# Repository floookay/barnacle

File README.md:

# barnacle

The barnacle is unibody ortho keyboard with an Alice-like split on the pinky columns and a fixed layout that's compatible with keycap set base kits.

## inspiration + backstory

The Boardrun series was my main inspiration for this project obviously. I desperately wanted to get an acrylic frosted purple Boardrun classic but things happend so that's not likely anymore unfortunatelly.

The creativity of designers with colorful keycap designs and interesting keyboards (like the TGR Alice) got me hooked with the hobby. I exclusively switched to non-rowstagger keyboards a couple of years ago and realized that I own a lot of beautiful keycaps that I love but can't use because of these weird non-symmetrical larger-than-1.5u mod key sizes per row. Most ergonomic keyboard designs that are trying to solve that issue, I don't find aesthetically pleasing or don't like the layout.  
So I've set out to create my own: the barnacle

## design goals

- 5x6 unibody ortho keyboard
- base kit compatibility
- 3d printable on 220mm build plates
- symmetric design (AMAP)
- outer thumb keys next to space bars
- easily expandable later on
- minimize stabilizer use

## layout

The main layout is fixed but the cores offer some variety. This is based on my Sol keymap but you can modify it in QMK of course.
<details>
<summary>layout</summary>

</details>

## pcb

This keyboard uses the [0xCB Helios](https://keeb.supply/products/0xcb-helios) as its controller. It's an affordable open-source pro-micro-compatible RP2040 controller with ESD protection and additional pins and features.

The pcbs where designed with KiCAD 8.0

### core pcb

You can use any core pcb with a shell. They are smaller than 100mmx100mm so it's relativly cheap to get a small batch made.

#### basic core

This core offers the following configurations:
- 9 keys
- 3 keys and a encoder with a big knob
- 3 keys and a 0.96" OLED screen
- 2 small encoders, 1 key and a 0.96" OLED screen
- a central encoder with the biggest knob

### shell pcb

- fixed layout, so I chose hotswap sockets
- rgb underglow
- per key rgb

## case

- 3mm acrylic bottom
- 5 degree typing angle
- designed for 3d printing
- sandwich mount
- exchangable core pieces

The case was designed with FreeCAD 0.21.2

## firmware

This keyboard is powered by QMK: <https://github.com/floookay/qmk_firmware/keyboards/barnacle>

## bom and assembly

For the bill of materials and assembly instructions see [here](./assembly.md).

## ideas and/or stuff I'd like to add in the future

### pcb

- [ ] *bluetooth core* with a nice!nano and without RGB (maybe with a safety cover toggle switch or sth)
- [ ] *trackball core* with PMW3360 sensor
- [ ] *trackpad core* with a 40mm GlidePoint Cirque Trackpad
- [ ] *oled core* with a large (colored?) OLED screen
- [ ] *lumberjack core* with a window and an integrated controller
- [ ] *rgb core* with a window and a rgb matrix
- [ ] *audio core* with a speaker/beeper

### case

- [ ] *brick core* with brick plate on top
- [ ] *wood core* with a cutout wooden window piece
- [ ] *gridfinity core* with a spot for a gridfinity bin
- [ ] *phone core* with a holder for (small) phones, maybe with a magsafe charger
- [ ] *change core* with a tray for coins and stuff
- [ ] *pen core* with a hole that fits a pen

### firmware

- [ ] *ZMK support* with the bluetooth core
- [ ] *vial and/or via support* once merged to main branch

## misc

> Why is it called barnacle?

I thought of hermit crabs when I was thinking of similiarities in nature. I stuck with the crab theme, but changed the name to barnacle, because it's a fun word to say out loud.

## acknowledgements

Huge thank you to ebastler and MarvFPV for the awesome [marbastlib](https://github.com/ebastler/marbastlib) library for KiCAD.

Thanks for reading and feel free to reach out to me or create PRs if you have any questions or things to improve upon.

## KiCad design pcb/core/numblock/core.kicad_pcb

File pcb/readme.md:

# pcb

## shell pcb

The shell has a fixed layout with hotswap sockets as well as RGB underglow und per key RBG leds.

## core pcb

You can use any core pcb with a shell. They are smaller than 100mmx100mm so it's relativly cheap to get a small batch made.

> [!NOTE]
> Every core has two jumpers at the top next to the controller. If you want to use RGB leds you will have to bridge either the left or right pads each.
> - Left jumper pad for the input pin: left (marked) for the Helios' pin 25, right for other controllers (D1)
> - Right jumper pad for the power source: left (marked) for raw/5V, right for 3.3V

### versatile core

This is a great starting point if you want to experiment with different layouts and don't care too much about hot swap ability.

The following configurations are supported:
- 9 keys
- 3 keys and a encoder with a big knob
- 3 keys and a 0.96"/1.3" OLED screen
- 2 small encoders, 1 key and a 0.96" OLED screen
- a central encoder with the biggest knob

> [!NOTE]
> There are two additional jumpers on this pcb. These are used so the GND pad of the encoder isn't connected to a column. If you want to use the adjacent key you'll have to close it.

### encoder core

This core has three top keys and a encoder beneath like the versatile core but with hot swap sockets.

### special core

This core exposes I2C and SPI pins and has a large cutout for mounting a trackball, trackpad or large oled to the core case (WIP).

### cute core

This core has centered 2x2 grid of keys with hot swap sockets.

### numpad core

This core has a 3x3 grid of keys with hot swap sockets (when possible) and an additional 0 key that can be snapped off.

### _template/ directory

The `_template/` directory contains the basic configuration if you want to create your own core pcb.

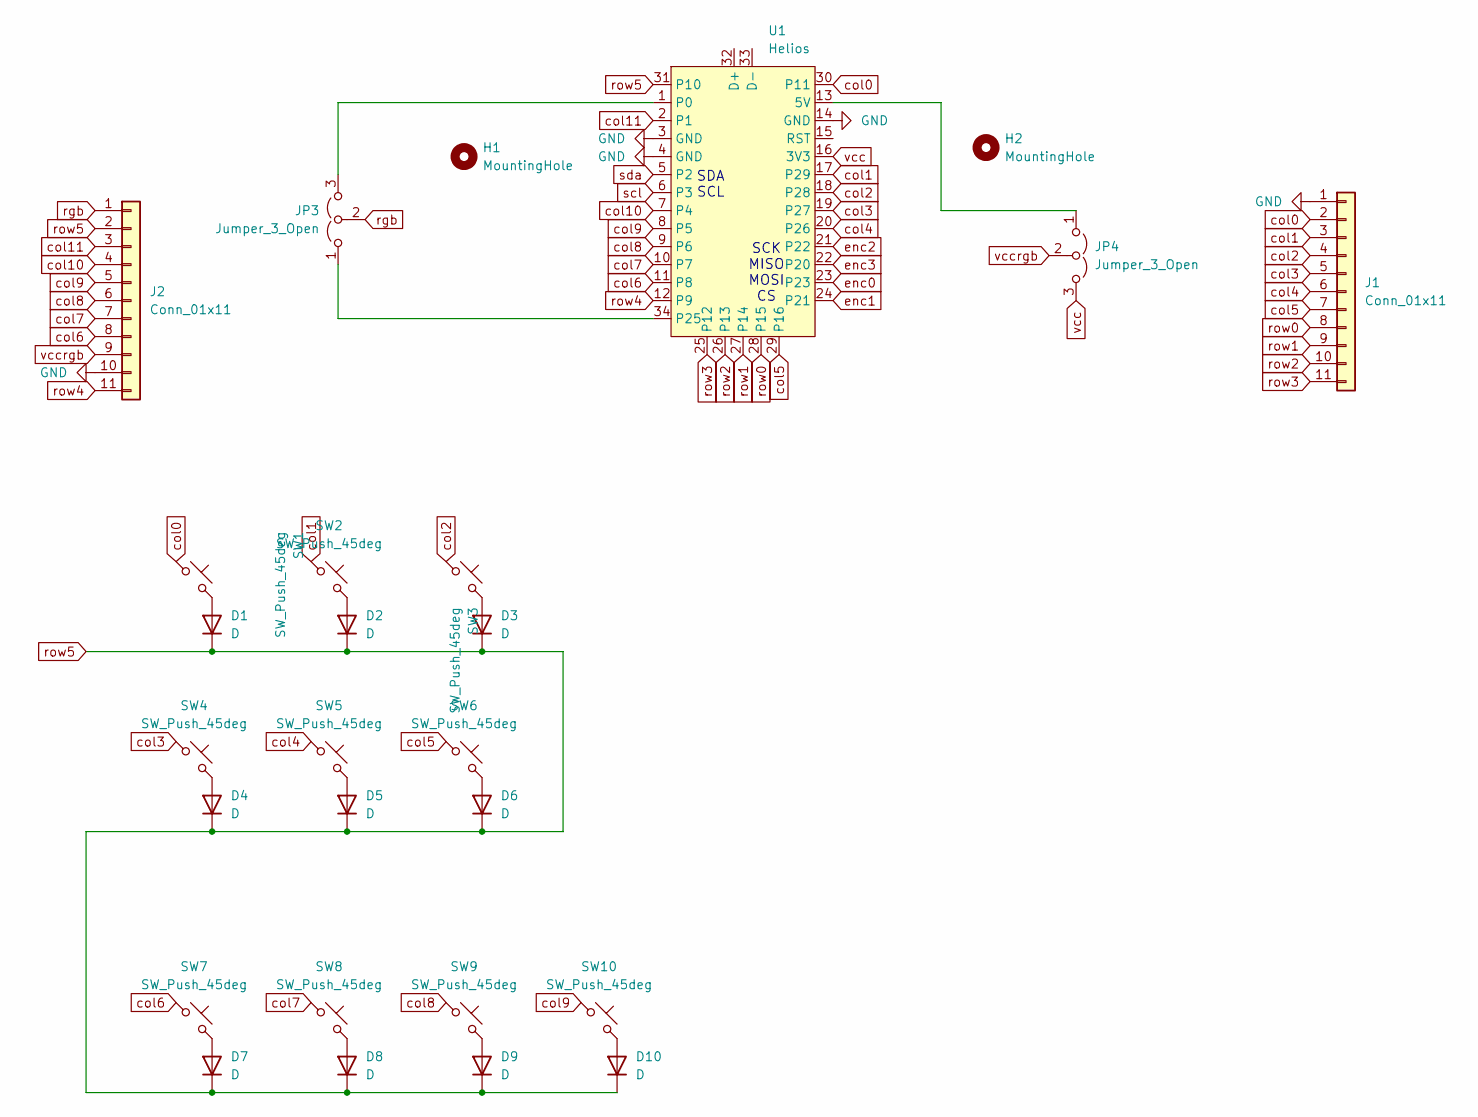
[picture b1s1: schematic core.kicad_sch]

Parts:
D1, D2, D3, D4, D5, D6, D7, D8, D9, D10: D; D_SOD-123-minimal
H1, H2: MountingHole; MountingHole_3.2mm_M3_DIN965_Pad
J1, J2: Conn_01x11; PinHeader_1x11_P2.54mm_Vertical
JP3, JP4: Jumper_3_Open; SolderJumper-3_P1.3mm_Open_RoundedPad1.0x1.5mm
SW1, SW3, SW4, SW5, SW6, SW7, SW8, SW9, SW10: SW_Push_45deg; SW_MX_HS_S_CPG151101S11_1u
SW2: SW_Push_45deg; SW_MX_1u
U1: Helios; Helios_AH_USBup

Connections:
GND: J1.1, J2.10, U1.3 (GND), U1.4 (GND), U1.14 (GND)
unnamed: D1.2 (A), SW1.2
unnamed: D2.2 (A), SW2.2
unnamed: D3.2 (A), SW3.2
unnamed: D4.2 (A), SW4.2
unnamed: D5.2 (A), SW5.2
unnamed: D6.2 (A), SW6.2
unnamed: D7.2 (A), SW7.2
unnamed: D8.2 (A), SW8.2
unnamed: D9.2 (A), SW9.2
unnamed: D10.2 (A), SW10.2
unnamed: JP3.1 (A), U1.34 (P25)
unnamed: JP3.3 (B), U1.1 (P0)
unnamed: JP4.1 (A), U1.13 (5V)
col0: J1.2, SW1.1, U1.30 (P11)
col1: J1.3, SW2.1, U1.17 (P29)
col2: J1.4, SW3.1, U1.18 (P28)
col3: J1.5, SW4.1, U1.19 (P27)
col4: J1.6, SW5.1, U1.20 (P26)
col5: J1.7, SW6.1, U1.29 (P16)
col6: J2.8, SW7.1, U1.11 (P8)
col7: J2.7, SW8.1, U1.10 (P7)
col8: J2.6, SW9.1, U1.9 (P6)
col9: J2.5, SW10.1, U1.8 (P5)
col10: J2.4, U1.7 (P4)
col11: J2.3, U1.2 (P1)
enc0: U1.23
enc1: U1.24 (P21)
enc2: U1.21 (P22)
enc3: U1.22 (P20)
rgb: J2.1, JP3.2 (C)
row0: J1.8, U1.28 (P15)
row1: J1.9, U1.27 (P14)
row2: J1.10, U1.26 (P13)
row3: J1.11, U1.25 (P12)
row4: J2.11, U1.12 (P9)
row5: D1.1 (K), D2.1 (K), D3.1 (K), D4.1 (K), D5.1 (K), D6.1 (K), D7.1 (K), D8.1 (K), D9.1 (K), D10.1 (K), J2.2, U1.31 (P10)
scl: U1.6 (P3)
sda: U1.5 (P2)
vcc: JP4.3 (B), U1.16 (3V3)
vccrgb: J2.9, JP4.2 (C)

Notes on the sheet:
SDA SCL
SCK MISO MOSI CS

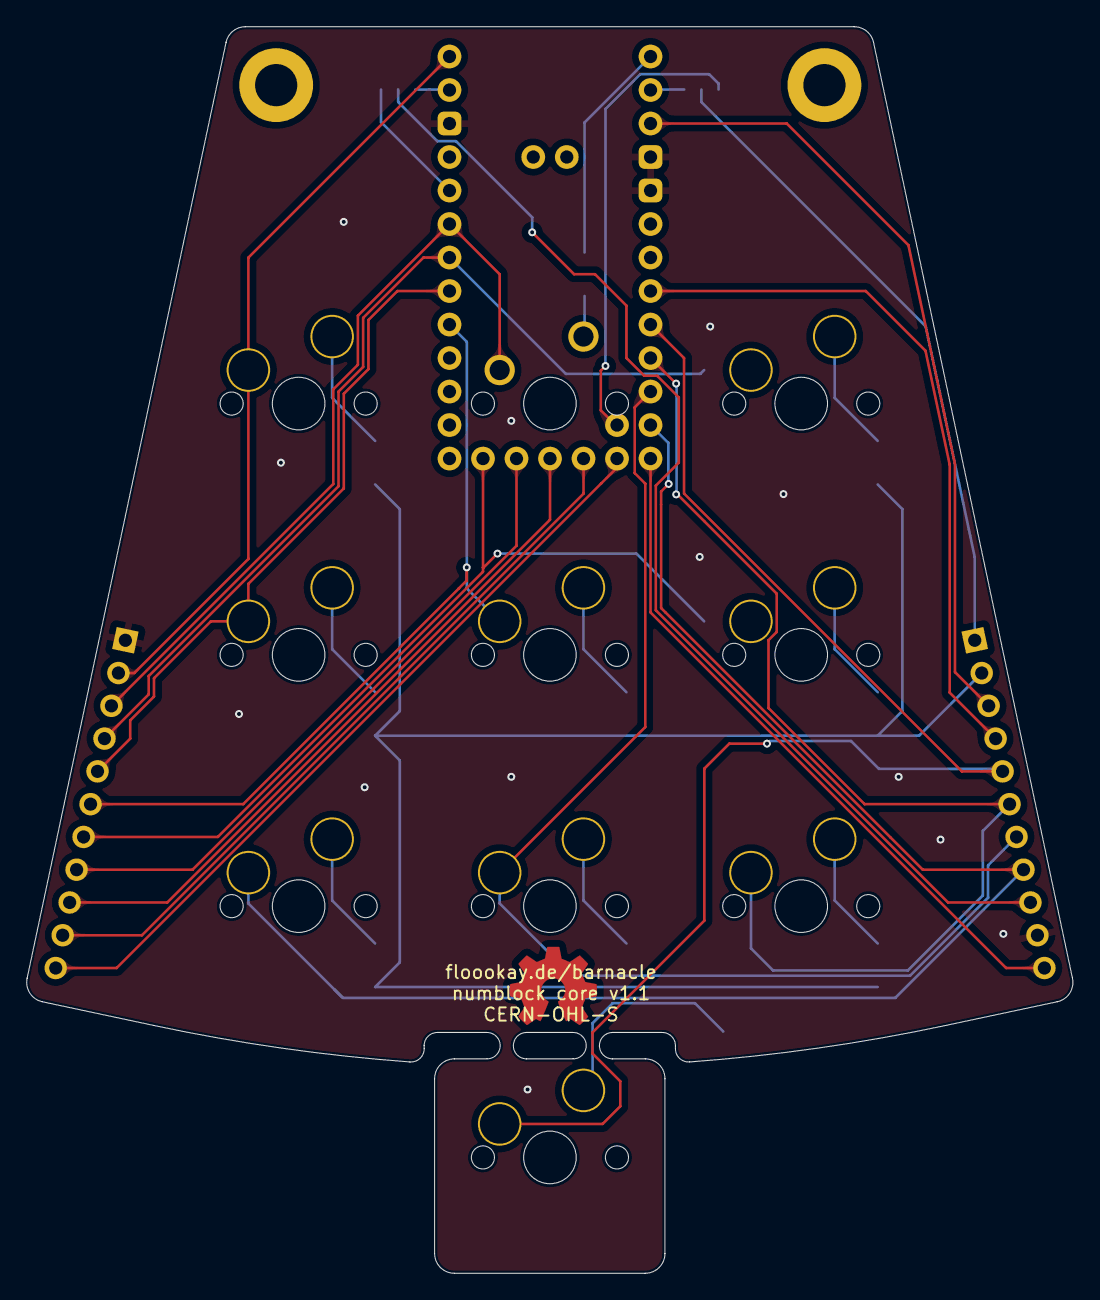
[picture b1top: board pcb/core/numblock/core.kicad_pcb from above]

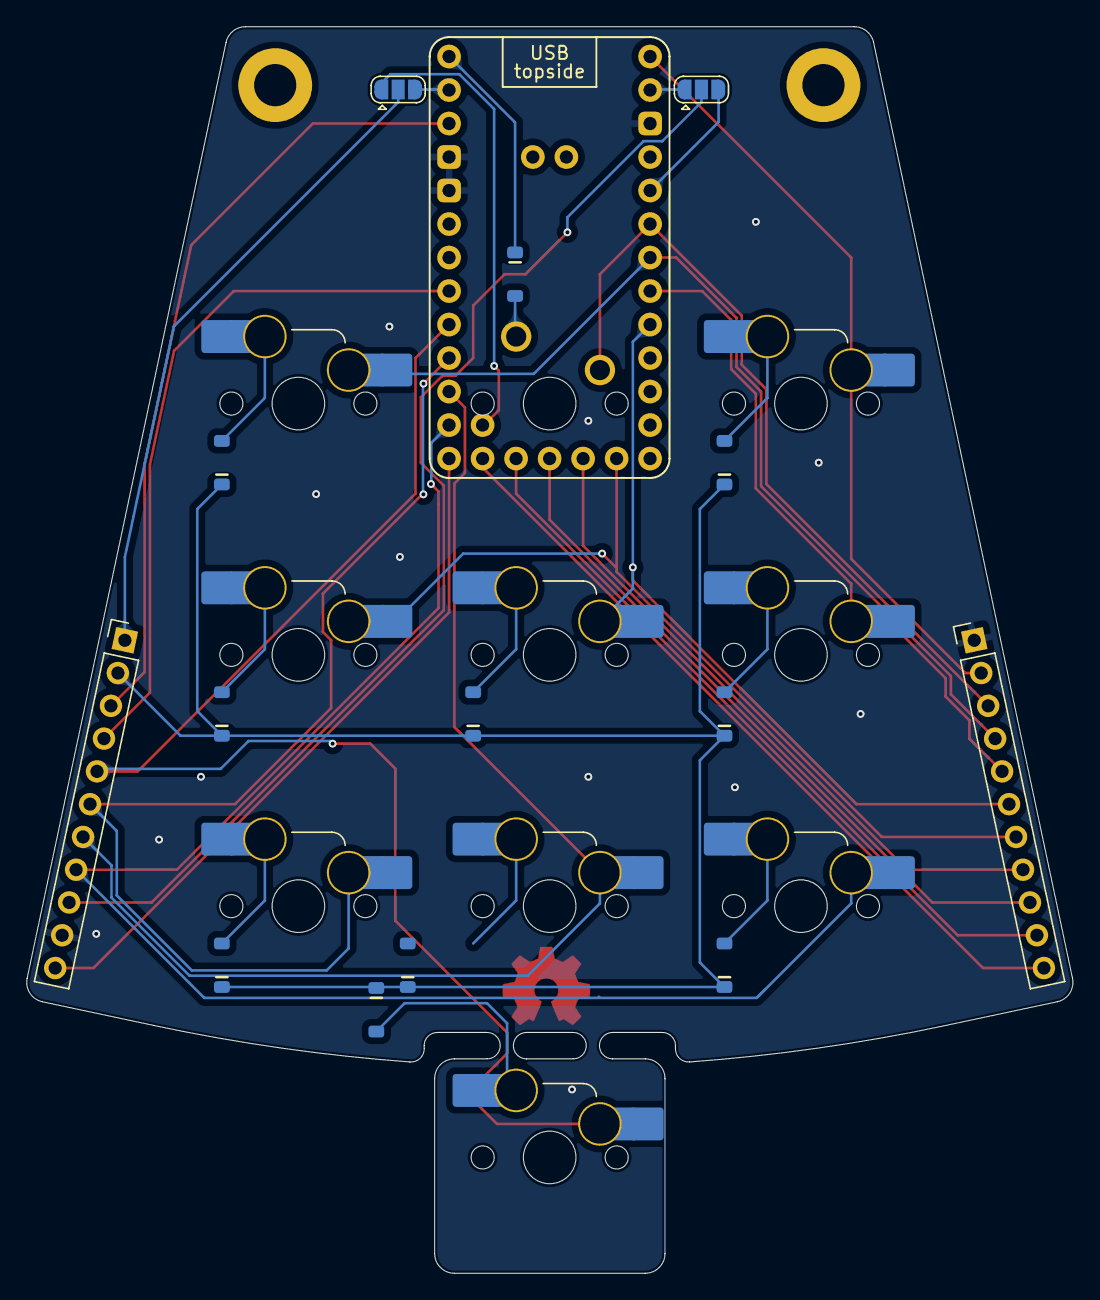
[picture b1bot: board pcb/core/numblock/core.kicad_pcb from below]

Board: 2 copper layers, 79.3 x 94.5 mm, 27 parts (24 on the bottom side), 35 nets.

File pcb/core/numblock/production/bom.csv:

Designator,Footprint,Quantity,Value,LCSC Part #
"D1, D2, D3, D4, D5, D6, D7, D8, D9",D_SOD-123-minimal,9,D,
"J1, J2",PinHeader_1x11_P2.54mm_Vertical,2,Conn_01x11,
"SW1, SW3, SW4, SW5, SW6, SW7, SW8, SW9",SW_MX_HS_S_CPG151101S11_1u,8,SW_Push_45deg,
SW2,SW_MX_1u,1,SW_Push_45deg,

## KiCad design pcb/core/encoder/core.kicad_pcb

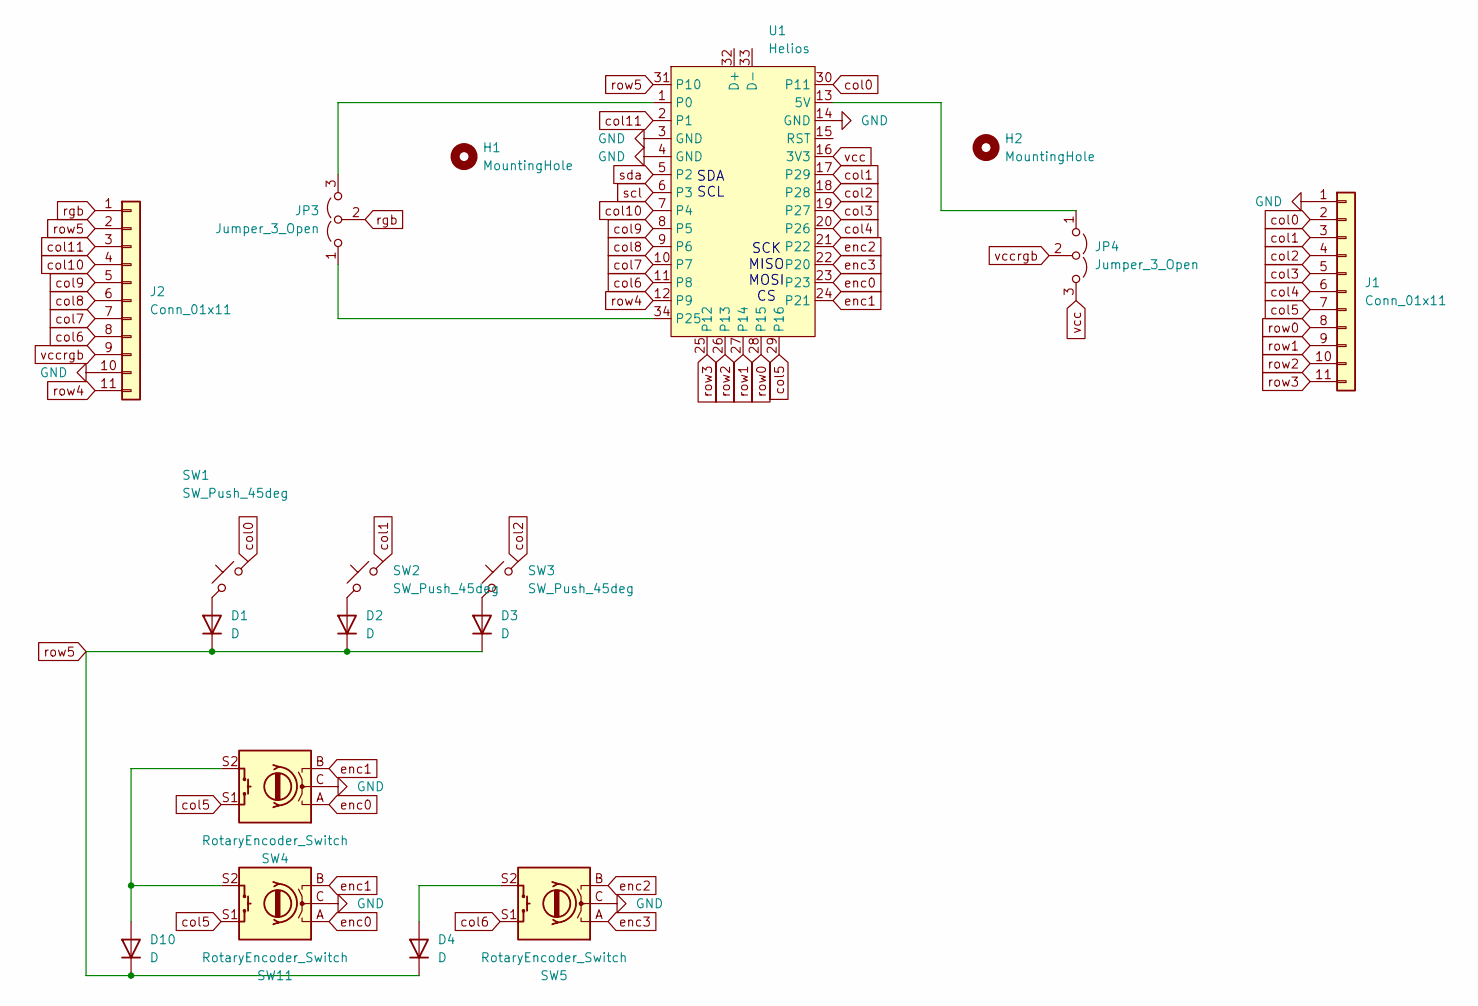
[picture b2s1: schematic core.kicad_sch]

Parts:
D1, D2, D3, D4, D10: D; D_SOD-123-minimal
H1, H2: MountingHole; MountingHole_3.2mm_M3_DIN965_Pad
J1, J2: Conn_01x11; PinHeader_1x11_P2.54mm_Vertical
JP3, JP4: Jumper_3_Open; SolderJumper-3_P1.3mm_Open_RoundedPad1.0x1.5mm
SW1, SW3: SW_Push_45deg; SW_MX_HS_S_CPG151101S11_1u
SW2: SW_Push_45deg; SW_MX_1u
SW4, SW5, SW11: RotaryEncoder_Switch; ROT_Alps_EC11E-Switch
U1: Helios; Helios_AH_USBup

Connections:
GND: J1.1, J2.10, SW4.C, SW5.C, SW11.C, U1.3 (GND), U1.4 (GND), U1.14 (GND)
unnamed: D1.2 (A), SW1.1
unnamed: D2.2 (A), SW2.1
unnamed: D3.2 (A), SW3.1
unnamed: D4.2 (A), SW5.S2
unnamed: D10.2 (A), SW4.S2, SW11.S2
unnamed: JP3.1 (A), U1.34 (P25)
unnamed: JP3.3 (B), U1.1 (P0)
unnamed: JP4.1 (A), U1.13 (5V)
col0: J1.2, SW1.2, U1.30 (P11)
col1: J1.3, SW2.2, U1.17 (P29)
col2: J1.4, SW3.2, U1.18 (P28)
col3: J1.5, U1.19 (P27)
col4: J1.6, U1.20 (P26)
col5: J1.7, SW4.S1, SW11.S1, U1.29 (P16)
col6: J2.8, SW5.S1, U1.11 (P8)
col7: J2.7, U1.10 (P7)
col8: J2.6, U1.9 (P6)
col9: J2.5, U1.8 (P5)
col10: J2.4, U1.7 (P4)
col11: J2.3, U1.2 (P1)
enc0: SW4.A, SW11.A, U1.23
enc1: SW4.B, SW11.B, U1.24 (P21)
enc2: SW5.B, U1.21 (P22)
enc3: SW5.A, U1.22 (P20)
rgb: J2.1, JP3.2 (C)
row0: J1.8, U1.28 (P15)
row1: J1.9, U1.27 (P14)
row2: J1.10, U1.26 (P13)
row3: J1.11, U1.25 (P12)
row4: J2.11, U1.12 (P9)
row5: D1.1 (K), D2.1 (K), D3.1 (K), D4.1 (K), D10.1 (K), J2.2, U1.31 (P10)
scl: U1.6 (P3)
sda: U1.5 (P2)
vcc: JP4.3 (B), U1.16 (3V3)
vccrgb: J2.9, JP4.2 (C)

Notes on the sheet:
SDA SCL
SCK MISO MOSI CS

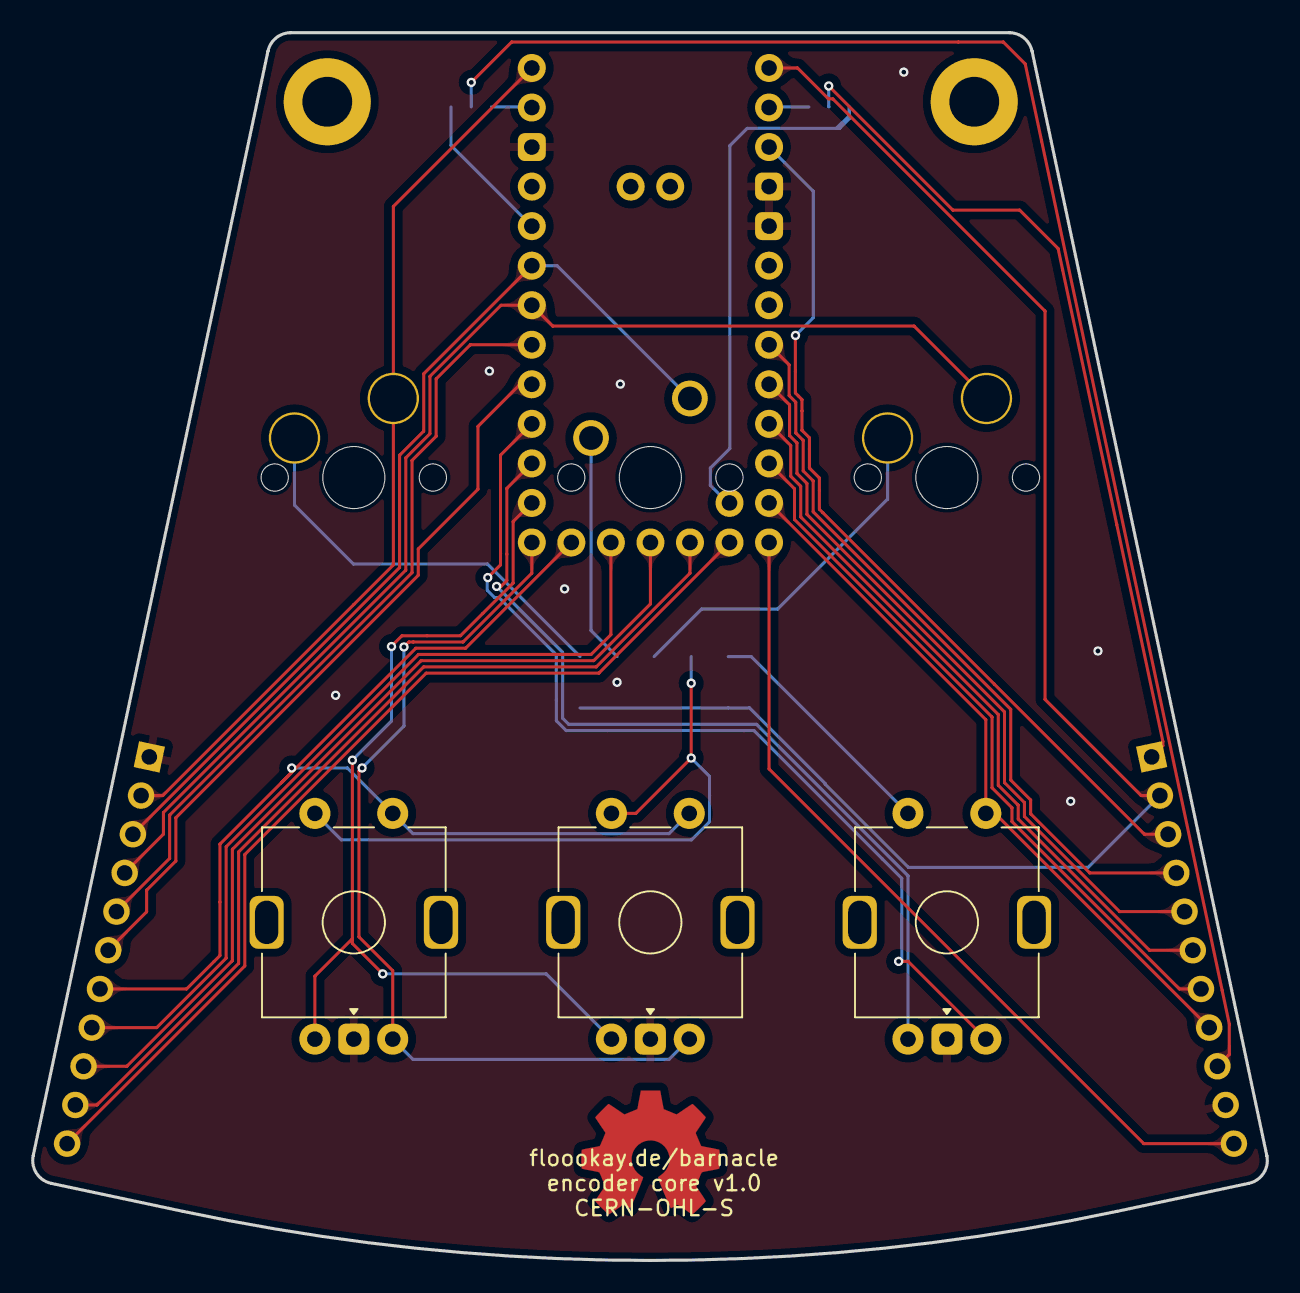
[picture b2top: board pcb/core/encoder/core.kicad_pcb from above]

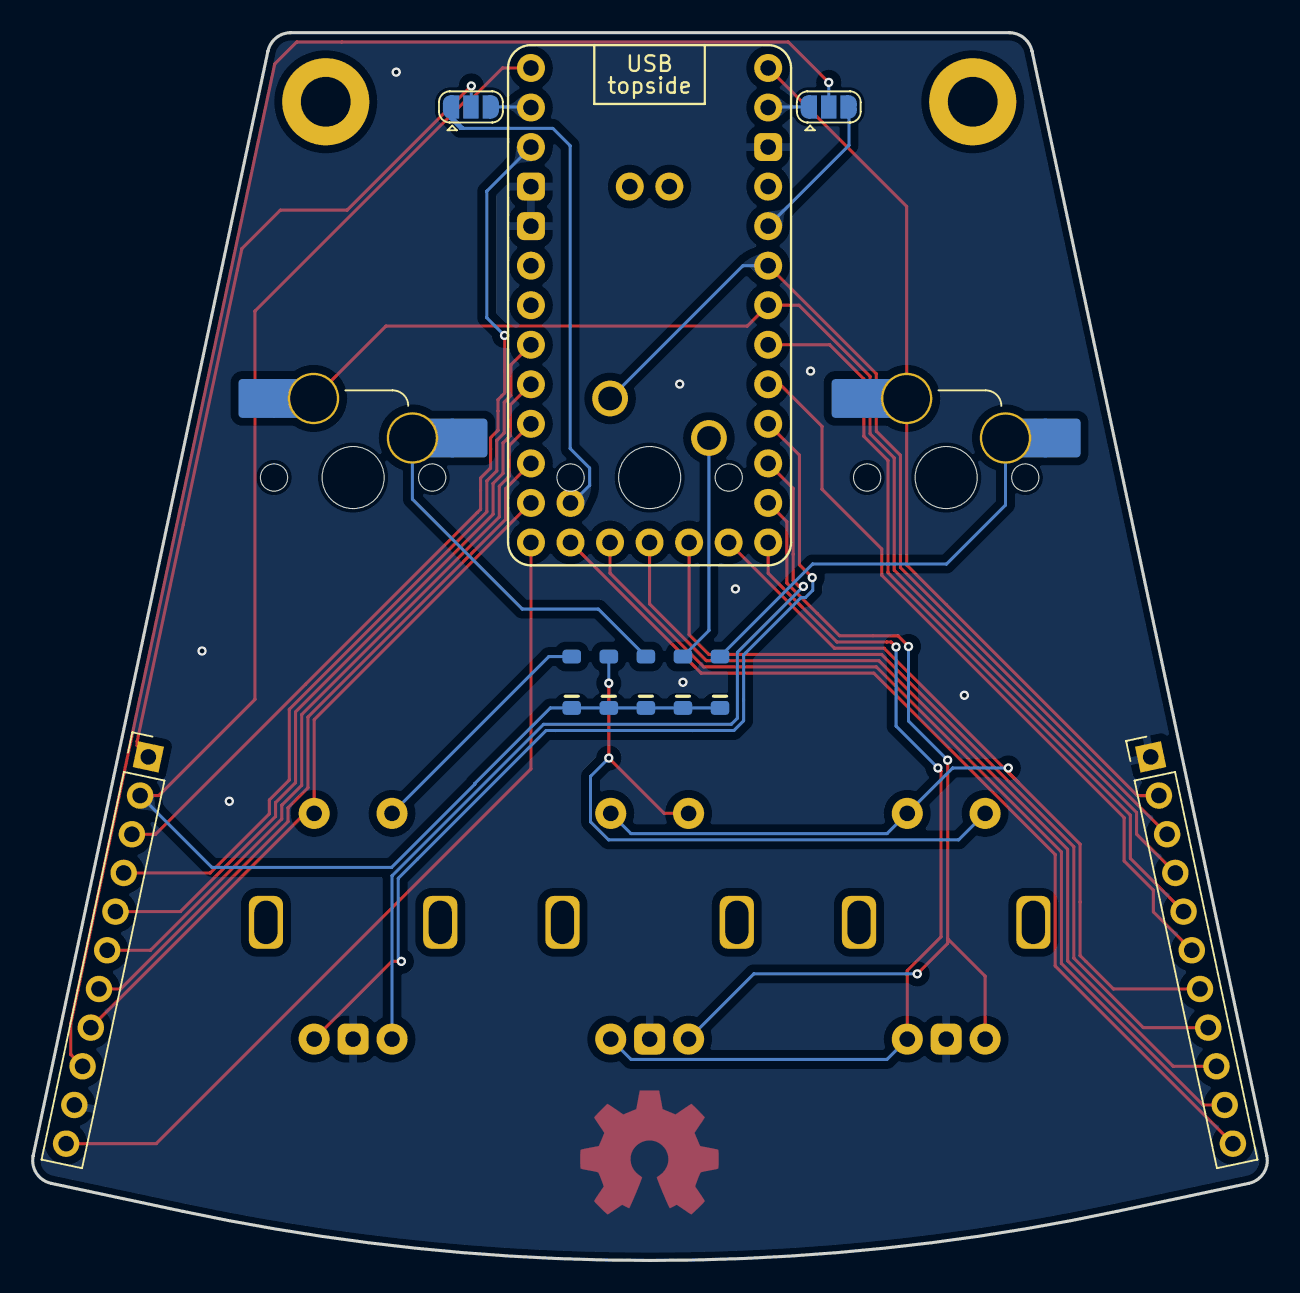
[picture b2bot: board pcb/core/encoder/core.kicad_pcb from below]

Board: 2 copper layers, 79.3 x 78.9 mm, 18 parts (12 on the bottom side), 34 nets.

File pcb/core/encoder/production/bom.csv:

Designator,Footprint,Quantity,Value,LCSC Part #
"D1, D10, D2, D3, D4",D_SOD-123-minimal,5,D,
"J1, J2",PinHeader_1x11_P2.54mm_Vertical,2,Conn_01x11,
"SW1, SW3",SW_MX_HS_S_CPG151101S11_1u,2,SW_Push_45deg,
"SW11, SW4, SW5",ROT_Alps_EC11E-Switch,3,RotaryEncoder_Switch,
SW2,SW_MX_1u,1,SW_Push_45deg,

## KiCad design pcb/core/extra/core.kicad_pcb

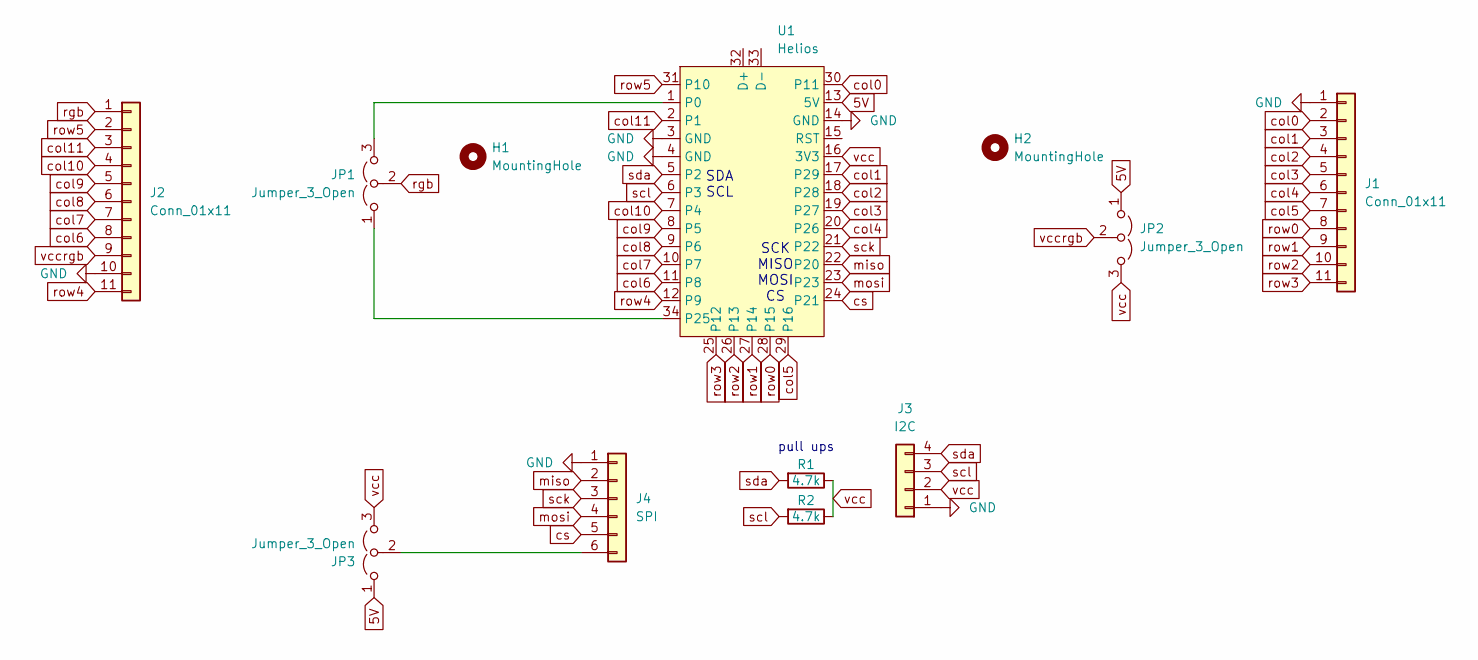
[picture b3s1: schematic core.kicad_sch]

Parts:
H1, H2: MountingHole; MountingHole_3.2mm_M3_DIN965_Pad
J1, J2: Conn_01x11; PinHeader_1x11_P2.54mm_Vertical
J3: I2C; PinHeader_1x04_P2.54mm_Vertical
J4: SPI; PinHeader_1x06_P2.54mm_Vertical
JP1, JP2, JP3: Jumper_3_Open; SolderJumper-3_P1.3mm_Open_RoundedPad1.0x1.5mm
R1, R2: 4.7k; R_Axial_DIN0207_L6.3mm_D2.5mm_P7.62mm_Horizontal; LCSC C269746
U1: Helios; Helios_AH_USBup

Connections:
5V: JP2.1 (A), JP3.1 (A), U1.13 (5V)
GND: J1.1, J2.10, J3.1, J4.1, U1.3 (GND), U1.4 (GND), U1.14 (GND)
unnamed: J4.6, JP3.2 (C)
unnamed: JP1.1 (A), U1.34 (P25)
unnamed: JP1.3 (B), U1.1 (P0)
col0: J1.2, U1.30 (P11)
col1: J1.3, U1.17 (P29)
col2: J1.4, U1.18 (P28)
col3: J1.5, U1.19 (P27)
col4: J1.6, U1.20 (P26)
col5: J1.7, U1.29 (P16)
col6: J2.8, U1.11 (P8)
col7: J2.7, U1.10 (P7)
col8: J2.6, U1.9 (P6)
col9: J2.5, U1.8 (P5)
col10: J2.4, U1.7 (P4)
col11: J2.3, U1.2 (P1)
cs: J4.5, U1.24 (P21)
miso: J4.2, U1.22 (P20)
mosi: J4.4, U1.23
rgb: J2.1, JP1.2 (C)
row0: J1.8, U1.28 (P15)
row1: J1.9, U1.27 (P14)
row2: J1.10, U1.26 (P13)
row3: J1.11, U1.25 (P12)
row4: J2.11, U1.12 (P9)
row5: J2.2, U1.31 (P10)
sck: J4.3, U1.21 (P22)
scl: J3.3, R2.2, U1.6 (P3)
sda: J3.4, R1.2, U1.5 (P2)
vcc: J3.2, JP2.3 (B), JP3.3 (B), R1.1, R2.1, U1.16 (3V3)
vccrgb: J2.9, JP2.2 (C)

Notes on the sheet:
pull ups
SDA SCL
SCK MISO MOSI CS

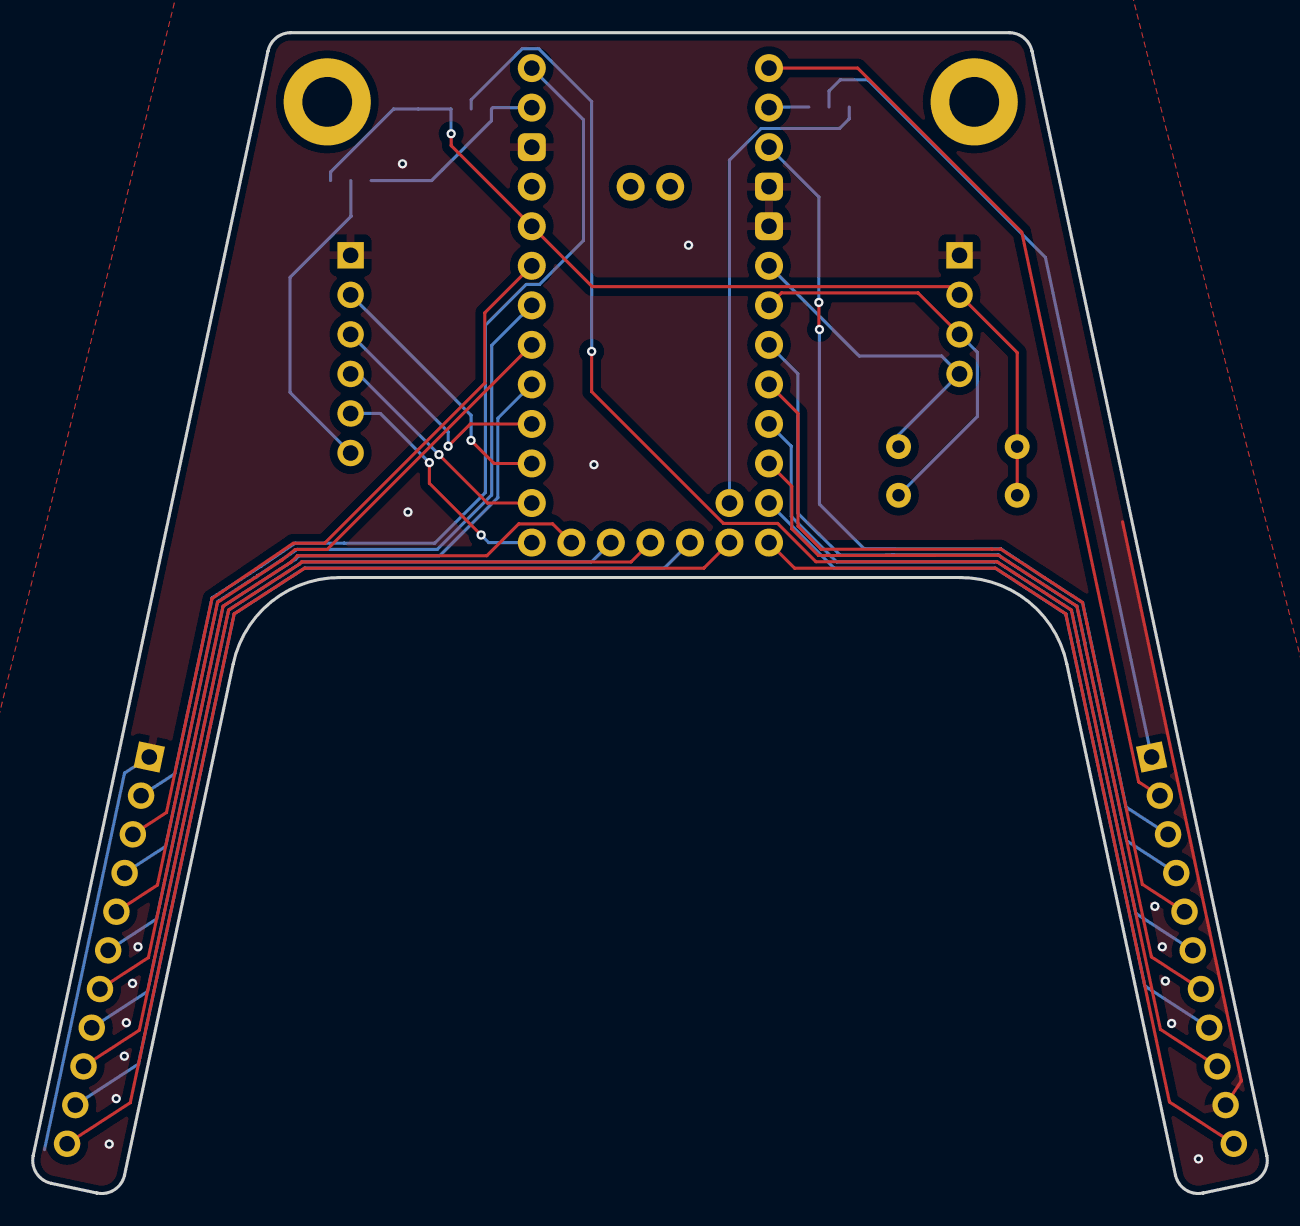
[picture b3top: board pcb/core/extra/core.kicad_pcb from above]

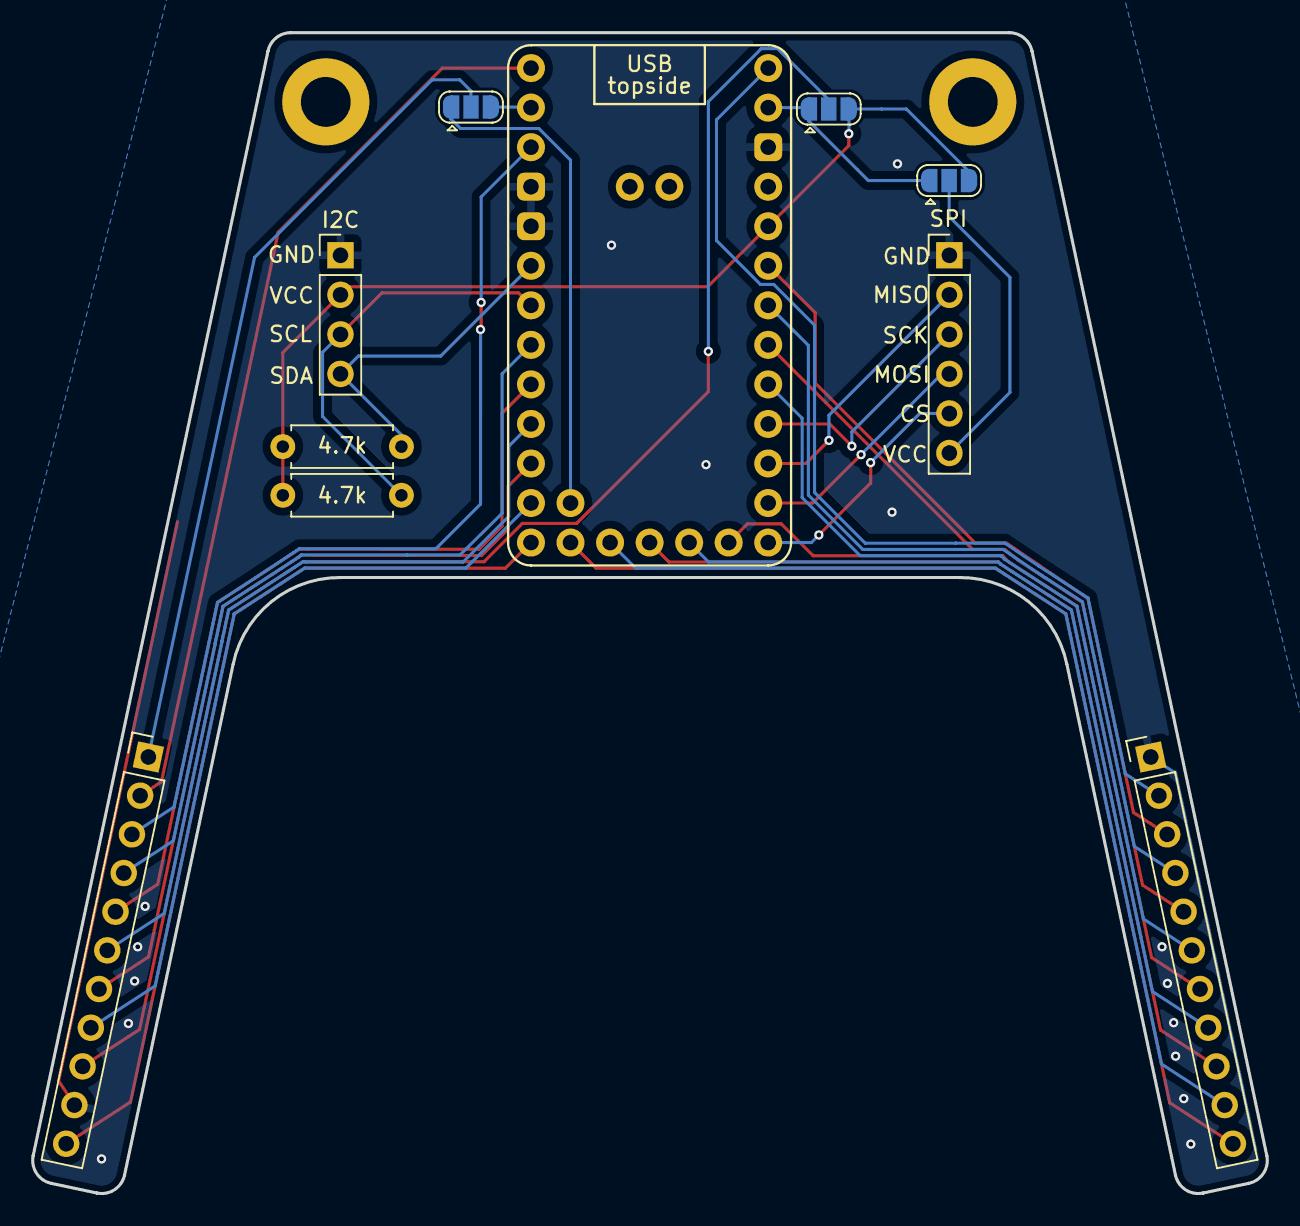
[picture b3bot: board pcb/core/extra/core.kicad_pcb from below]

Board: 2 copper layers, 79.3 x 74.6 mm, 12 parts (10 on the bottom side), 32 nets.

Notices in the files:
pcb/core/encoder/core.kicad_pcb:
CERN-OHL-S
